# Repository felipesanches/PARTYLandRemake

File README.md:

PARTYLandRemake
===============

PARTY Land Remake - Building a real-life playfield replica of the PARTY Land pinball table from the Amiga game Pinball Fantasies

Dependencies
------------

> sudo pip install solidpinball  
> sudo apt-get install openscad  

Hacking
-------

Use the command "make preview" to generate only the SCAD file.  
Then, open outputs/SCAD/partyland_assembly.scad using Openscad and 
make sure you enable the "Automatic Reload and Preview" option in the
"Design" menu. This will make it much easier to see the results of modifications to
the "CAD/PARTYLandRemake.py" file as soon as you re-run "make preview"  

There are lots of parts that still need to be modeled. The proper place for the parts
models is in the SolidPinball code repository. Feel free to contribute code to this repository
or to SolidPinball. I'll review any pul requests as soon as possible.

Licensing
---------

Although the original design of the PARTY Land pinball table does not belong to me, the 3d models,
SVG/DXF vectors and SCAD scripts here are authored by me (Felipe Sanches <juca@members.fsf.org>) and
I publish these files under the GNU GPLv3 or later so that other DIY pinball enthusiasts can
build upon my work and hopefully we can have more people building their own homebrew pinball machines. :-)

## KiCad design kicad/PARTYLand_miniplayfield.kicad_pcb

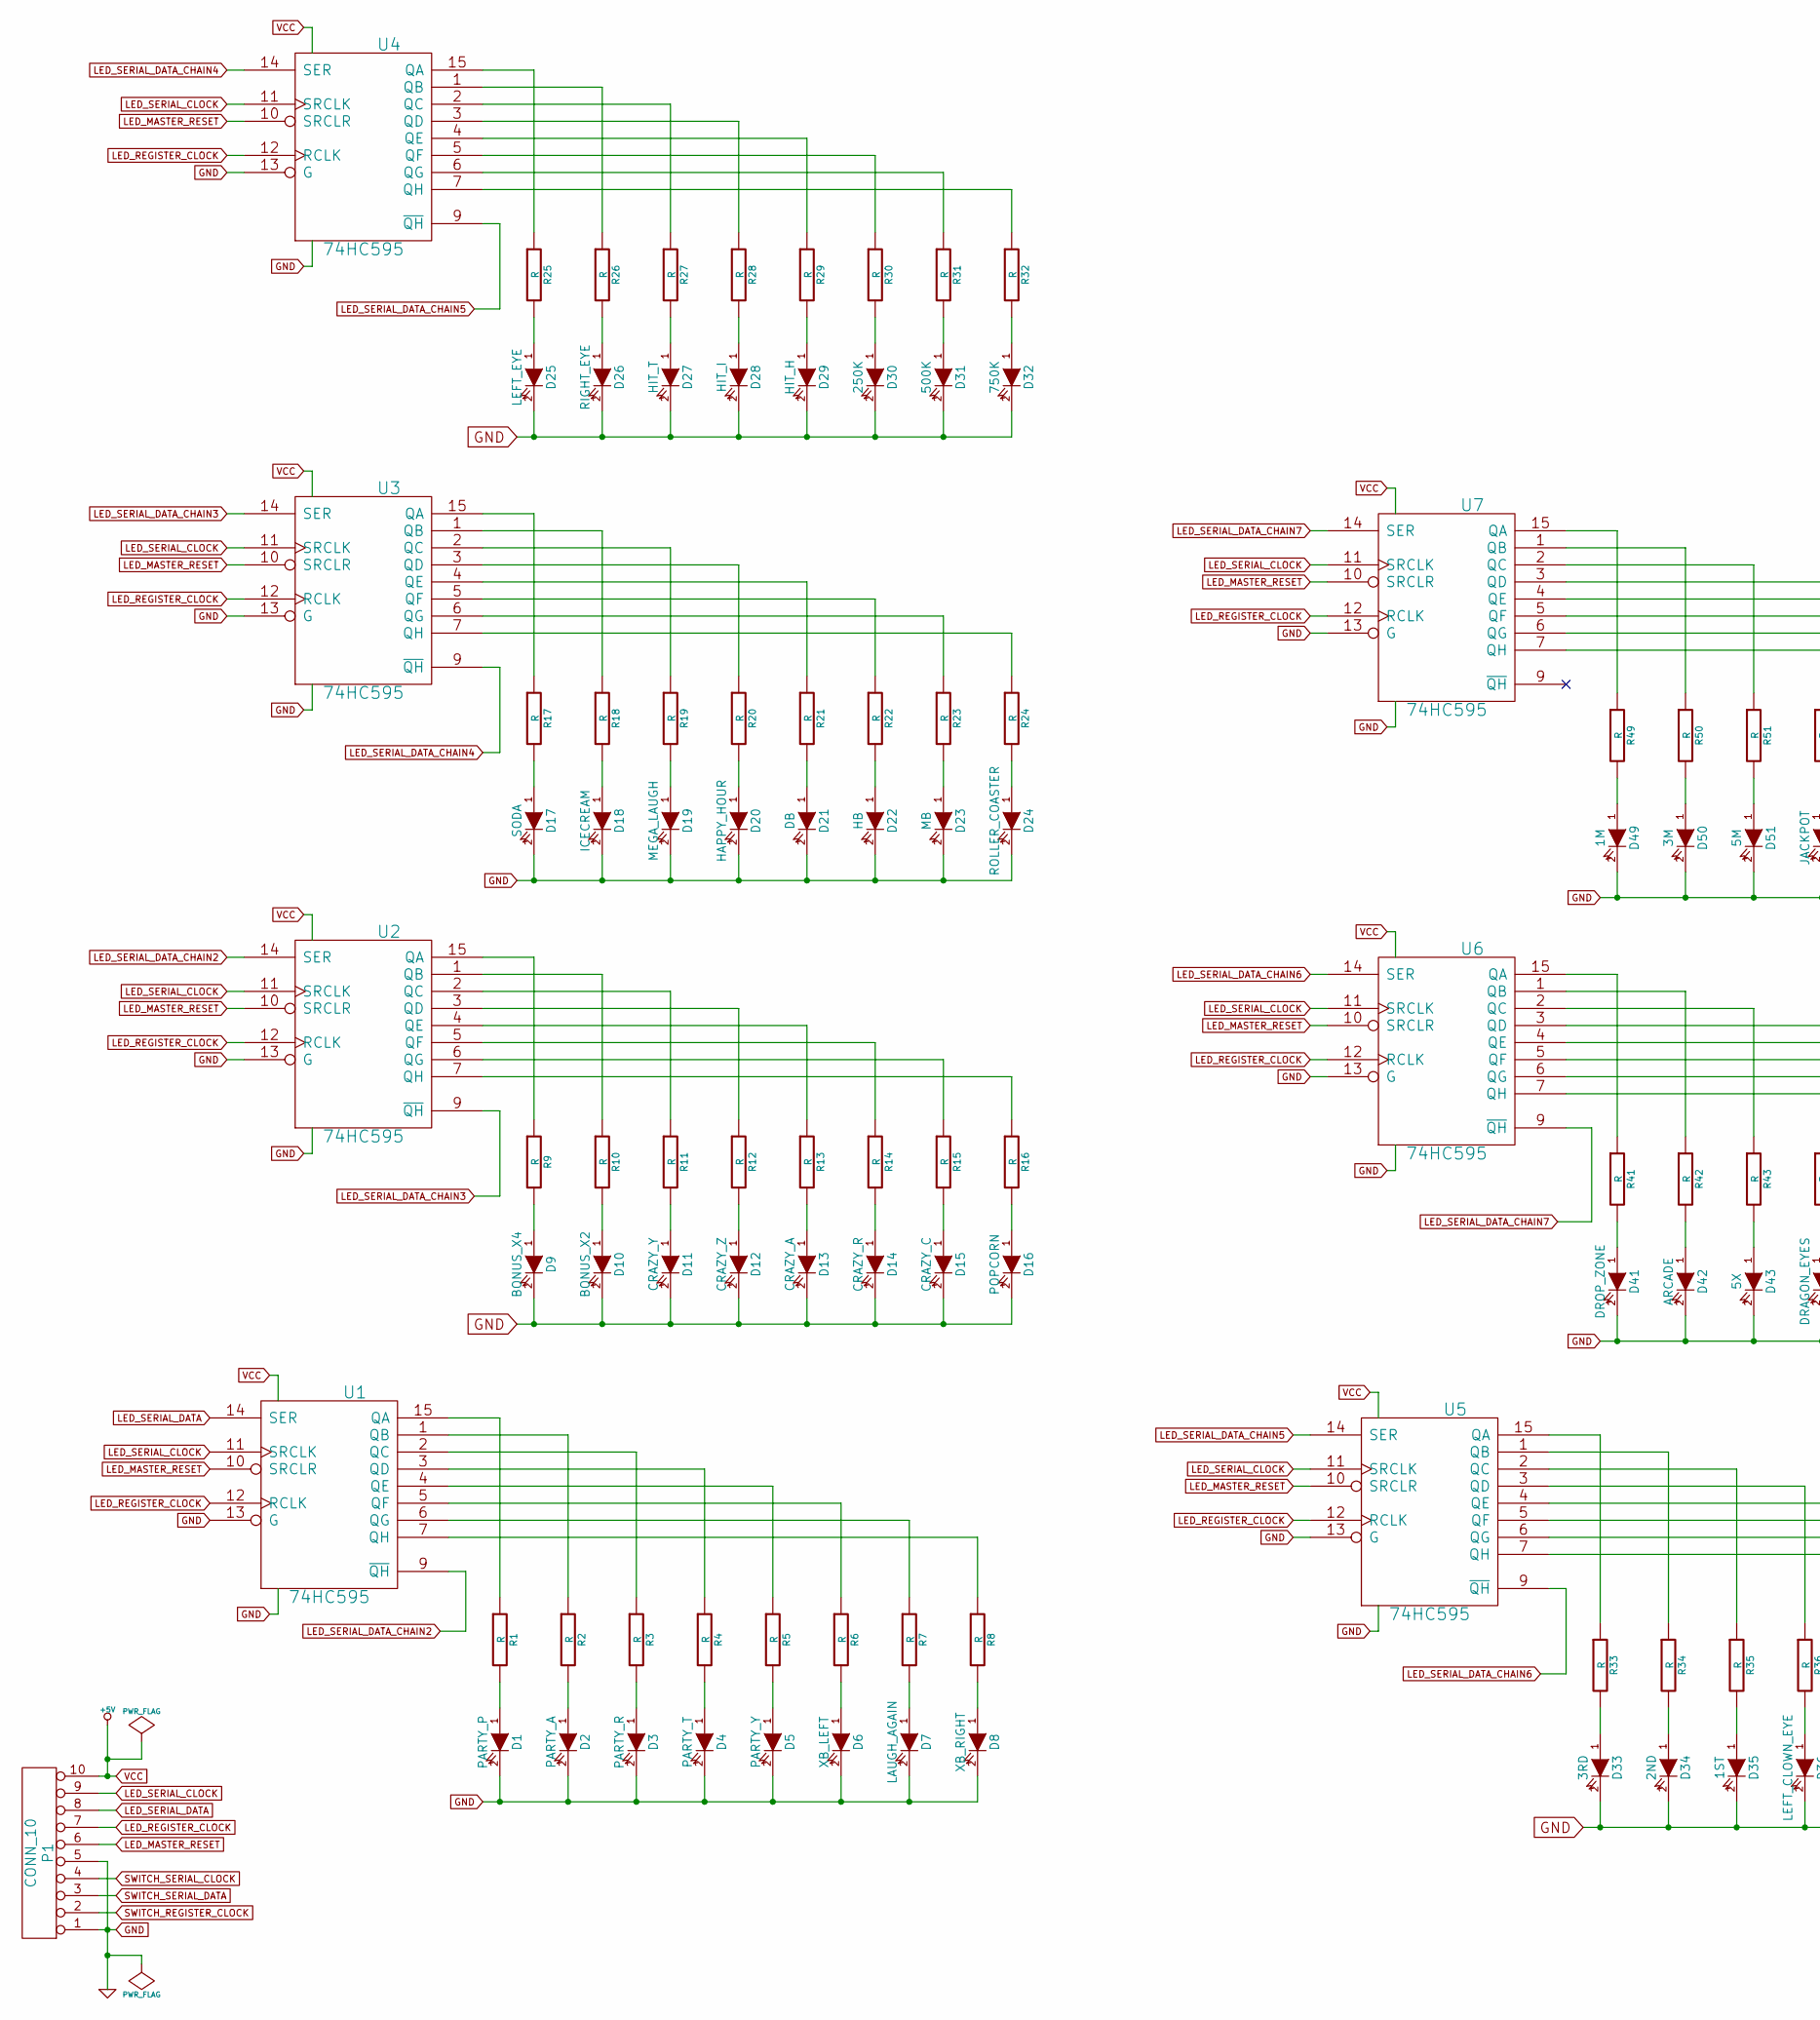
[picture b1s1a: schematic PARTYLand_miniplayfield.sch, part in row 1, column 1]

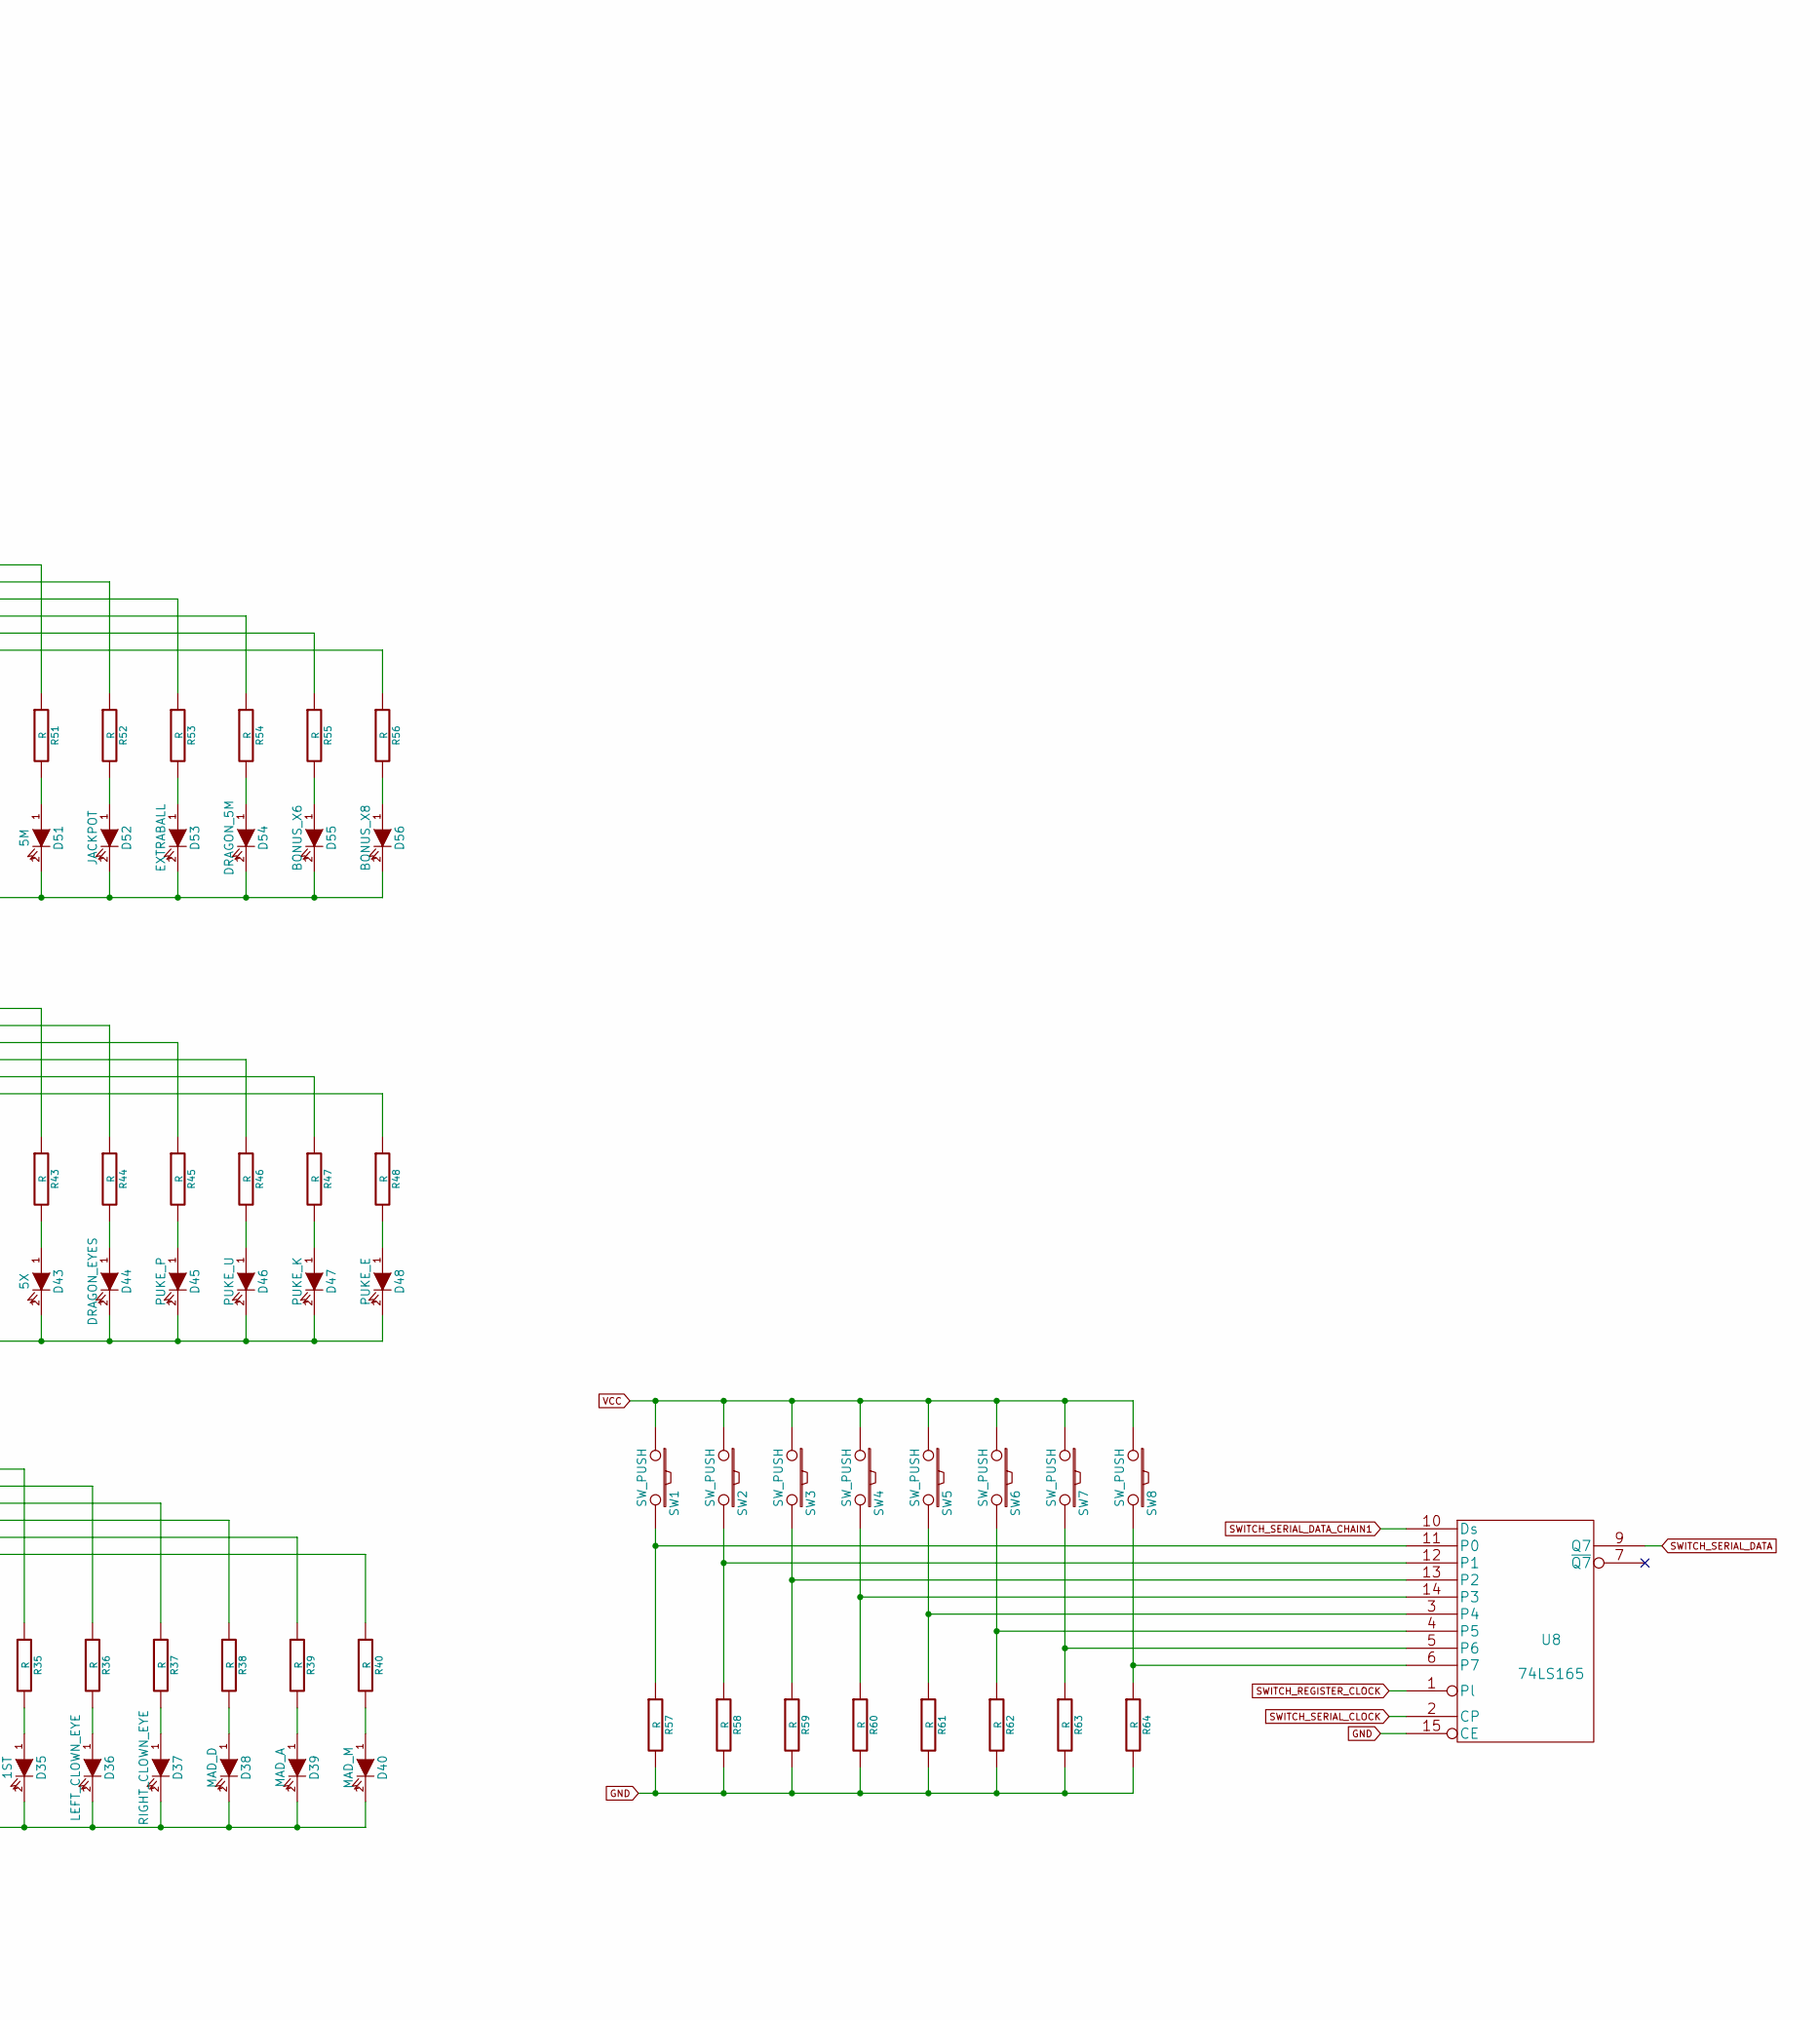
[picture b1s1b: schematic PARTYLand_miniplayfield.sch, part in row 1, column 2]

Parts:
D1: PARTY_P; LED-3MM
D2: PARTY_A; LED-3MM
D3: PARTY_R; LED-3MM
D4: PARTY_T; LED-3MM
D5: PARTY_Y; LED-3MM
D6: XB_LEFT; LED-3MM
D7: LAUGH_AGAIN; LED-3MM
D8: XB_RIGHT; LED-3MM
D9: BONUS_X4; LED-3MM
D10: BONUS_X2; LED-3MM
D11: CRAZY_Y; LED-3MM
D12: CRAZY_Z; LED-3MM
D13: CRAZY_A; LED-3MM
D14: CRAZY_R; LED-3MM
D15: CRAZY_C; LED-3MM
D16: POPCORN; LED-3MM
D17: SODA; LED-3MM
D18: ICECREAM; LED-3MM
D19: MEGA_LAUGH; LED-3MM
D20: HAPPY_HOUR; LED-3MM
D21: DB; LED-3MM
D22: HB; LED-3MM
D23: MB; LED-3MM
D24: ROLLER_COASTER; LED-3MM
D25: LEFT_EYE; LED-3MM
D26: RIGHT_EYE; LED-3MM
D27: HIT_T; LED-3MM
D28: HIT_I; LED-3MM
D29: HIT_H; LED-3MM
D30: 250K; LED-3MM
D31: 500K; LED-3MM
D32: 750K; LED-3MM
D33: 3RD; LED-3MM
D34: 2ND; LED-3MM
D35: 1ST; LED-3MM
D36: LEFT_CLOWN_EYE; LED-3MM
D37: RIGHT_CLOWN_EYE; LED-3MM
D38: MAD_D; LED-3MM
D39: MAD_A; LED-3MM
D40: MAD_M; LED-3MM
D41: DROP_ZONE; LED-3MM
D42: ARCADE; LED-3MM
D43: 5X; LED-3MM
D44: DRAGON_EYES; LED-3MM
D45: PUKE_P; LED-3MM
D46: PUKE_U; LED-3MM
D47: PUKE_K; LED-3MM
D48: PUKE_E; LED-3MM
D49: 1M; LED-3MM
D50: 3M; LED-3MM
D51: 5M; LED-3MM
D52: JACKPOT; LED-3MM
D53: EXTRABALL; LED-3MM
D54: DRAGON_5M; LED-3MM
D55: BONUS_X6; LED-3MM
D56: BONUS_X8; LED-3MM
P1: CONN_10; Pin_Header_Angled_1x10
R1, R2, R3, R4, R5, R6, R7, R8, R9, R10, R11, R12, R13, R14, R15, R16, R17, R18, R19, R20, R21, R22, R23, R24, R25, R26, R27, R28, R29, R30, R31, R32, R33, R34, R35, R36, R37, R38, R39, R40, R41, R42, R43, R44, R45, R46, R47, R48, R49, R50, R51, R52, R53, R54, R55, R56, R57, R58, R59, R60, R61, R62, R63, R64: R; R3
SW1, SW2, SW3, SW4, SW5, SW6, SW7, SW8: SW_PUSH; SW_PUSH_SMALL
U1, U2, U3, U4, U5, U6, U7: 74HC595; DIP-16__300_ELL
U8: 74LS165; DIP-16__300_ELL

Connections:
GND: D1.2 (K), D2.2 (K), D3.2 (K), D4.2 (K), D5.2 (K), D6.2 (K), D7.2 (K), D8.2 (K), D9.2 (K), D10.2 (K), D11.2 (K), D12.2 (K), D13.2 (K), D14.2 (K), D15.2 (K), D16.2 (K), D17.2 (K), D18.2 (K), D19.2 (K), D20.2 (K), D21.2 (K), D22.2 (K), D23.2 (K), D24.2 (K), D25.2 (K), D26.2 (K), D27.2 (K), D28.2 (K), D29.2 (K), D30.2 (K), D31.2 (K), D32.2 (K), D33.2 (K), D34.2 (K), D35.2 (K), D36.2 (K), D37.2 (K), D38.2 (K), D39.2 (K), D40.2 (K), D41.2 (K), D42.2 (K), D43.2 (K), D44.2 (K), D45.2 (K), D46.2 (K), D47.2 (K), D48.2 (K), D49.2 (K), D50.2 (K), D51.2 (K), D52.2 (K), D53.2 (K), D54.2 (K), D55.2 (K), D56.2 (K), P1.1, P1.5, R57.2, R58.2, R59.2, R60.2, R61.2, R62.2, R63.2, R64.2, U1.8 (GND), U1.13 (G), U2.8 (GND), U2.13 (G), U3.8 (GND), U3.13 (G), U4.8 (GND), U4.13 (G), U5.8 (GND), U5.13 (G), U6.8 (GND), U6.13 (G), U7.8 (GND), U7.13 (G), U8.8 (GND), U8.15 (CE)
LED_MASTER_RESET: P1.6, U1.10 (SRCLR), U2.10 (SRCLR), U3.10 (SRCLR), U4.10 (SRCLR), U5.10 (SRCLR), U6.10 (SRCLR), U7.10 (SRCLR)
LED_REGISTER_CLOCK: P1.7, U1.12 (RCLK), U2.12 (RCLK), U3.12 (RCLK), U4.12 (RCLK), U5.12 (RCLK), U6.12 (RCLK), U7.12 (RCLK)
LED_SERIAL_CLOCK: P1.9, U1.11 (SRCLK), U2.11 (SRCLK), U3.11 (SRCLK), U4.11 (SRCLK), U5.11 (SRCLK), U6.11 (SRCLK), U7.11 (SRCLK)
LED_SERIAL_DATA: P1.8, U1.14 (SER)
LED_SERIAL_DATA_CHAIN2: U1.9 (~QH), U2.14 (SER)
LED_SERIAL_DATA_CHAIN3: U2.9 (~QH), U3.14 (SER)
LED_SERIAL_DATA_CHAIN4: U3.9 (~QH), U4.14 (SER)
LED_SERIAL_DATA_CHAIN5: U4.9 (~QH), U5.14 (SER)
LED_SERIAL_DATA_CHAIN6: U5.9 (~QH), U6.14 (SER)
LED_SERIAL_DATA_CHAIN7: U6.9 (~QH), U7.14 (SER)
unnamed: D1.1 (A), R1.2
unnamed: D2.1 (A), R2.2
unnamed: D3.1 (A), R3.2
unnamed: D4.1 (A), R4.2
unnamed: D5.1 (A), R5.2
unnamed: D6.1 (A), R6.2
unnamed: D7.1 (A), R7.2
unnamed: D8.1 (A), R8.2
unnamed: D9.1 (A), R9.2
unnamed: D10.1 (A), R10.2
unnamed: D11.1 (A), R11.2
unnamed: D12.1 (A), R12.2
unnamed: D13.1 (A), R13.2
unnamed: D14.1 (A), R14.2
unnamed: D15.1 (A), R15.2
unnamed: D16.1 (A), R16.2
unnamed: D17.1 (A), R17.2
unnamed: D18.1 (A), R18.2
unnamed: D19.1 (A), R19.2
unnamed: D20.1 (A), R20.2
unnamed: D21.1 (A), R21.2
unnamed: D22.1 (A), R22.2
unnamed: D23.1 (A), R23.2
unnamed: D24.1 (A), R24.2
unnamed: D25.1 (A), R25.2
unnamed: D26.1 (A), R26.2
unnamed: D27.1 (A), R27.2
unnamed: D28.1 (A), R28.2
unnamed: D29.1 (A), R29.2
unnamed: D30.1 (A), R30.2
unnamed: D31.1 (A), R31.2
unnamed: D32.1 (A), R32.2
unnamed: D33.1 (A), R33.2
unnamed: D34.1 (A), R34.2
unnamed: D35.1 (A), R35.2
unnamed: D36.1 (A), R36.2
unnamed: D37.1 (A), R37.2
unnamed: D38.1 (A), R38.2
unnamed: D39.1 (A), R39.2
unnamed: D40.1 (A), R40.2
unnamed: D41.1 (A), R41.2
unnamed: D42.1 (A), R42.2
unnamed: D43.1 (A), R43.2
unnamed: D44.1 (A), R44.2
unnamed: D45.1 (A), R45.2
unnamed: D46.1 (A), R46.2
unnamed: D47.1 (A), R47.2
unnamed: D48.1 (A), R48.2
unnamed: D49.1 (A), R49.2
unnamed: D50.1 (A), R50.2
unnamed: D51.1 (A), R51.2
unnamed: D52.1 (A), R52.2
unnamed: D53.1 (A), R53.2
unnamed: D54.1 (A), R54.2
unnamed: D55.1 (A), R55.2
unnamed: D56.1 (A), R56.2
unnamed: R1.1, U1.15 (QA)
unnamed: R2.1, U1.1 (QB)
unnamed: R3.1, U1.2 (QC)
unnamed: R4.1, U1.3 (QD)
unnamed: R5.1, U1.4 (QE)
unnamed: R6.1, U1.5 (QF)
unnamed: R7.1, U1.6 (QG)
unnamed: R8.1, U1.7 (QH)
unnamed: R9.1, U2.15 (QA)
unnamed: R10.1, U2.1 (QB)
unnamed: R11.1, U2.2 (QC)
unnamed: R12.1, U2.3 (QD)
unnamed: R13.1, U2.4 (QE)
unnamed: R14.1, U2.5 (QF)
unnamed: R15.1, U2.6 (QG)
unnamed: R16.1, U2.7 (QH)
unnamed: R17.1, U3.15 (QA)
unnamed: R18.1, U3.1 (QB)
unnamed: R19.1, U3.2 (QC)
unnamed: R20.1, U3.3 (QD)
unnamed: R21.1, U3.4 (QE)
unnamed: R22.1, U3.5 (QF)
unnamed: R23.1, U3.6 (QG)
unnamed: R24.1, U3.7 (QH)
unnamed: R25.1, U4.15 (QA)
unnamed: R26.1, U4.1 (QB)
unnamed: R27.1, U4.2 (QC)
unnamed: R28.1, U4.3 (QD)
unnamed: R29.1, U4.4 (QE)
unnamed: R30.1, U4.5 (QF)
unnamed: R31.1, U4.6 (QG)
unnamed: R32.1, U4.7 (QH)
unnamed: R33.1, U5.15 (QA)
unnamed: R34.1, U5.1 (QB)
unnamed: R35.1, U5.2 (QC)
unnamed: R36.1, U5.3 (QD)
unnamed: R37.1, U5.4 (QE)
unnamed: R38.1, U5.5 (QF)
unnamed: R39.1, U5.6 (QG)
unnamed: R40.1, U5.7 (QH)
unnamed: R41.1, U6.15 (QA)
unnamed: R42.1, U6.1 (QB)
unnamed: R43.1, U6.2 (QC)
unnamed: R44.1, U6.3 (QD)
unnamed: R45.1, U6.4 (QE)
unnamed: R46.1, U6.5 (QF)
unnamed: R47.1, U6.6 (QG)
unnamed: R48.1, U6.7 (QH)
unnamed: R49.1, U7.15 (QA)
unnamed: R50.1, U7.1 (QB)
unnamed: R51.1, U7.2 (QC)
unnamed: R52.1, U7.3 (QD)
unnamed: R53.1, U7.4 (QE)
unnamed: R54.1, U7.5 (QF)
unnamed: R55.1, U7.6 (QG)
unnamed: R56.1, U7.7 (QH)
unnamed: R57.1, SW1.2, U8.11 (P0)
unnamed: R58.1, SW2.2, U8.12 (P1)
unnamed: R59.1, SW3.2, U8.13 (P2)
unnamed: R60.1, SW4.2, U8.14 (P3)
unnamed: R61.1, SW5.2, U8.3 (P4)
unnamed: R62.1, SW6.2, U8.4 (P5)
unnamed: R63.1, SW7.2, U8.5 (P6)
unnamed: R64.1, SW8.2, U8.6 (P7)
SWITCH_REGISTER_CLOCK: P1.2, U8.1 (Pl)
SWITCH_SERIAL_CLOCK: P1.4, U8.2 (CP)
SWITCH_SERIAL_DATA: P1.3, U8.9 (Q7)
SWITCH_SERIAL_DATA_CHAIN1: U8.10 (Ds)
VCC: P1.10, SW1.1, SW2.1, SW3.1, SW4.1, SW5.1, SW6.1, SW7.1, SW8.1, U1.16 (VCC), U2.16 (VCC), U3.16 (VCC), U4.16 (VCC), U5.16 (VCC), U6.16 (VCC), U7.16 (VCC), U8.16 (VCC)

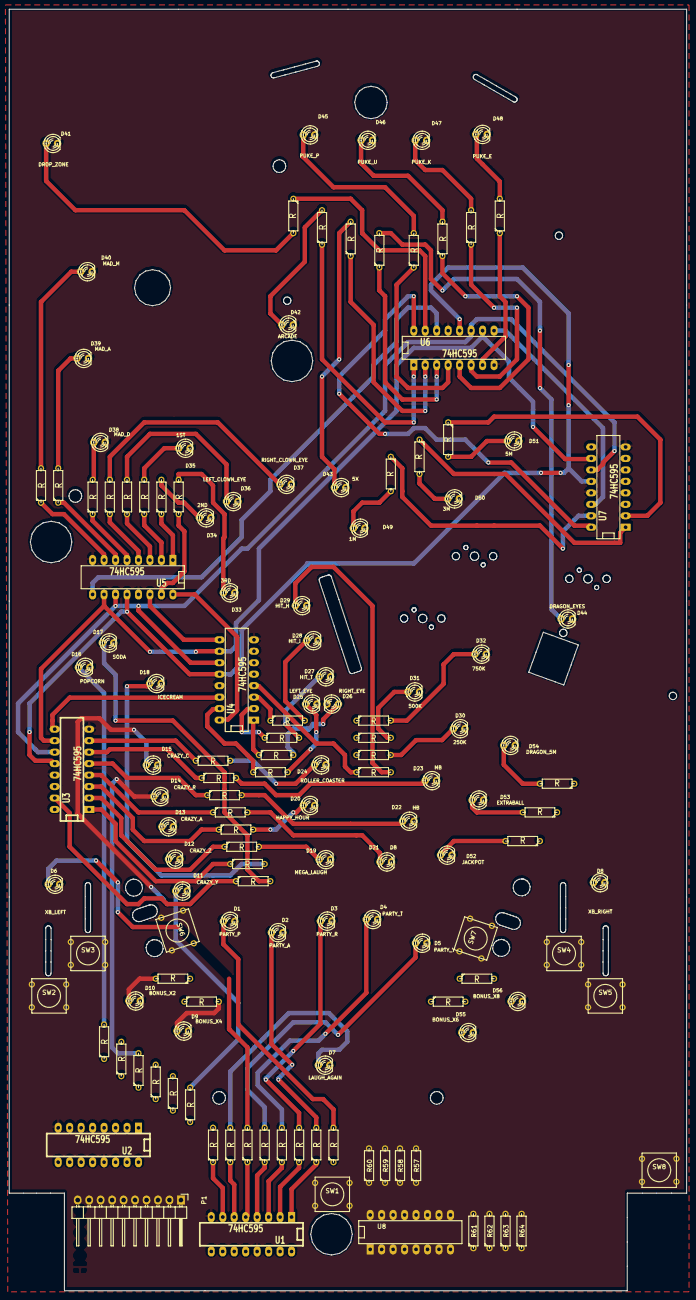
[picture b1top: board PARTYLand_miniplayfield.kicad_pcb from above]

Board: 2 copper layers, 150.0 x 283.8 mm, 137 parts (0 on the bottom side), 135 nets.

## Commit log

2014-10-16 initial build system and playfield scad boilerplate
2014-10-16 documenting dependencies
2014-10-16 adding line breaks in README.me
2014-10-16 fixing "dependencies" header in README.md
2014-10-16 fixing markdown syntax
2014-10-17 Starting to define the correct positions of the pinball parts (porting them from the SCAD file in the how-to-build-a-pinball GoogleCode repository)
2014-10-17 add "make preview" target and document it in the "Hacking" session of README.md
2014-10-17 Add comments to the main python file
2014-10-17 declaring playfield inserts
2014-10-17 licensing info
2014-10-17 fix minor english mistake do->does
2014-10-18 add ball launcher (requires building and installing SolidPinball from git)
2014-10-19 declaring rollover switches
2014-10-19 fixing the overall dimentions of the playfield
2014-10-21 adding an image to the README.md file
2014-10-21 fixing typo in the image url
2014-11-19 initial KiCAD project for the LED controller board
2014-11-21 Creating silk footprints with the party land artwork in order to place the LEDs correctly in the PCB. The holes/layout footprint is intended to be used as the board outline so the PCB will hav ethis 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
2014-11-21 Added the playfield outline (footprint drawing, still not the actual drill outline) Also tweaked the PCB metadata and the overall footprints positioning.
2014-11-21 Added a second group of LEDs using a second daisychained shift register. WIP on positioning the footprints on the PCB
2014-11-22 Adding more LED circuitry to the PARTYLand miniplayfield.
2014-11-22 A few more LEDs in the PARTYLand mini-playfield PCB.
2014-11-23 Finished placing all LEDs in the miniplayfield schematics and pcb layout. Also added propper PCB cut edges and ground planes for copper fill.
2014-11-23 ignoring kicad temp/autosave files
2014-11-23 Should KiCAD *-cache.lib files be under version control? I am not sure yet. So lets keep it here.
2014-11-23 .gitignore: ignoring the outputs directory that is generated by our Makefile
2014-11-24 wip: tracing the minipinball PCB
2015-04-01 * changing the connector size to also carry the switch control signals * resizing all labels to avoid overlap of neighbouring labels
2015-04-05 work in progress...
2018-10-01 fix DXF relative-path
2020-08-25 Travis setup + some small fixes to latest version of Solid Python
